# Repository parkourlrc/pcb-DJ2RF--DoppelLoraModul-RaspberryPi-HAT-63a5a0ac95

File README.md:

# English below

# DoppelLoraModul-RaspberryPi-HAT
Raspberry HAT for Nerdverlag LoRa Analyser or any other projects 
# Doppel-LoRa-HAT für Raspberry Pi

Dieses KiCad-Projekt enthält die Schaltung und das Leiterplattenlayout für ein Raspberry-Pi-HAT mit zwei unabhängigen 
LoRa-Funkmodulen auf Basis des **Semtech SX1262**.

Die Platine wurde für den gleichzeitigen Betrieb eines 433-MHz- und eines 863/868-MHz-Moduls entwickelt. 
Beide Funkmodule verwenden den gemeinsamen SPI0-Bus des Raspberry Pi, besitzen jedoch getrennte Chip-Select-, 
Reset-, Busy-, Interrupt- und HF-Umschaltleitungen.

Das HAT ist insbesondere für den Einsatz mit dem **LoRa MeshRadio Analyzer** und weiteren 
Raspberry-Pi-basierten LoRa-Empfangs- und Analyseprojekten vorgesehen.

---

## Unterstützte Funkmodule

Die Platine ist für folgende Waveshare-Core1262-Module ausgelegt:

- **Waveshare Core1262-LF**
  - Frequenzbereich: 410 bis 510 MHz
  - vorgesehen für Anwendungen im 433-MHz-Bereich

- **Waveshare Core1262-HF**
  - Frequenzbereich: 850 bis 930 MHz
  - vorgesehen für Anwendungen im 863-/868-MHz-Bereich

Beide Module basieren auf dem SX1262 und besitzen dieselbe mechanische sowie elektrische Anschlussbelegung.

---

## SPI-Anbindung

Beide SX1262-Module verwenden gemeinsam:

| Signal | Raspberry Pi GPIO | Physischer Pin |
|---|---:|---:|
| SPI0 MOSI | GPIO10 | Pin 19 |
| SPI0 MISO | GPIO9 | Pin 21 |
| SPI0 SCLK | GPIO11 | Pin 23 |

Die Module werden über getrennte Chip-Select-Leitungen angesprochen.

### 863-/868-MHz-Modul

| Funktion | Raspberry Pi GPIO | Physischer Pin |
|---|---:|---:|
| Chip Select | GPIO8 / CE0 | Pin 24 |
| Reset | GPIO22 | Pin 15 |
| Busy | GPIO23 | Pin 16 |
| DIO1 | GPIO24 | Pin 18 |
| RXEN | GPIO25 | Pin 22 |
| TXEN | GPIO5 | Pin 29 |

Linux-Gerät:

/dev/spidev0.0
433-MHz-Modul
Funktion	Raspberry Pi GPIO	Physischer Pin
Chip Select	GPIO7 / CE1	Pin 26
Reset	GPIO17	Pin 11
Busy	GPIO27	Pin 13
DIO1	GPIO18	Pin 12
RXEN	GPIO6	Pin 31
TXEN	GPIO13	Pin 33

Linux-Gerät:

/dev/spidev0.1
Funktionsprinzip

Die beiden LoRa-Module können unabhängig voneinander konfiguriert und gleichzeitig betrieben werden.

Typische Verwendung:

433-MHz-Modul für LoRa-Verbindungen im 70-cm-Bereich
863-/868-MHz-Modul für Sensoren, Telemetrie und ISM-LoRa-Anwendungen
paralleler Empfang auf beiden Frequenzbereichen
Einsatz als Funk-Frontend für den LoRa MeshRadio Analyzer
Entwicklung eigener Raspberry-Pi-LoRa-Anwendungen

Die Antennen werden direkt an den U.FL-/IPEX-Anschlüssen der jeweiligen Core1262-Module angeschlossen.

HAT-ID-EEPROM

Inhalt des Repositorys

Das Repository enthält die wesentlichen KiCad-Projektdateien:

*.kicad_pro
*.kicad_sch
*.kicad_pcb
fp-lib-table
sym-lib-table
Nerdverlag.pretty/

Eigene Symbole und Footprints werden zusammen mit dem Projekt gespeichert, damit der Schaltplan und das
Leiterplattenlayout auch auf anderen Rechnern vollständig geöffnet werden können.

Automatisch erzeugte KiCad-Backups, Sperrdateien und persönliche Arbeitsplatzdateien werden nicht versioniert.

Voraussetzungen

Zum Bearbeiten des Projekts wird eine aktuelle KiCad-Version empfohlen.

Das Projekt wurde mit KiCad 10 erstellt.

Für den späteren Betrieb auf dem Raspberry Pi müssen SPI und die GPIO-Schnittstellen aktiviert sein.

Kontrolle unter Linux:

ls -l /dev/spidev0.0 /dev/spidev0.1
ls -l /dev/gpiochip*

Der verwendete Benutzer sollte Mitglied der Gruppen spi und gpio sein.

Projektstatus

Das Projekt befindet sich in aktiver Entwicklung.

Vor einer Fertigung sollten mindestens folgende Punkte geprüft werden:

KiCad ERC ohne relevante Fehler
KiCad DRC ohne relevante Fehler
korrekte Footprints und Padnummern
ausreichende Leiterbahnbreiten für die Stromversorgung
vollständig gefüllte GND-Flächen
korrekte Bestückungsbezeichnungen für LF- und HF-Modul
mechanische Abstände zum Raspberry Pi
vollständige Gerber- und Bohrdatenausgabe

Eine Fertigung sollte immer auf Grundlage eines abschließend geprüften Versionsstands erfolgen.

Hinweis zum Funkbetrieb

Für den Funkbetrieb gelten die jeweils nationalen Vorschriften zu Frequenzbereichen,
Sendeleistungen, Bandbreiten und zulässigen Anwendungen.

Der Betreiber ist selbst dafür verantwortlich, die gesetzlichen Bestimmungen und
gegebenenfalls die für den Amateurfunk geltenden Regelungen einzuhalten.

Die Platine selbst stellt lediglich die technische Hardwareplattform bereit.

Lizenz und Nutzung

Dieses Projekt ist für eigene Entwicklungs-, Forschungs- und Ausbildungszwecke vorgesehen.

Eine kommerzielle Nutzung, Weitergabe oder Fertigung ist nur nach vorheriger Zustimmung des Rechteinhabers gestattet,
sofern keine separate Lizenzdatei etwas anderes festlegt.

## Author

**Friedrich Riedhammer – DJ2RF**  
**Nerdverlag**

[Visit Nerdverlag](https://nerdverlag.com)

[You can get the Software LoRa Analyser for free](https://nerdverlag.com/?page_id=892)

Email: [fritz@nerdverlag.com](mailto:fritz@nerdverlag.com)

---

© 2026 Nerdverlag  
Friedrich Riedhammer  
All rights reserved.

# English

# Dual LoRa HAT for Raspberry Pi

This KiCad project contains the schematic and PCB layout for a Raspberry Pi HAT with two independent
LoRa radio modules based on the **Semtech SX1262**.

The board was designed for the simultaneous operation of one 433 MHz module and one 863/868 MHz module.
Both radio modules share the Raspberry Pi SPI0 bus, while using separate chip-select,
reset, busy, interrupt, and RF switch control lines.

The HAT is primarily intended for use with the **LoRa MeshRadio Analyzer**
and other Raspberry Pi-based LoRa receiver and analysis projects.

---

## Supported Radio Modules

The board is designed for the following Waveshare Core1262 modules:

- **Waveshare Core1262-LF**
  - Frequency range: 410 to 510 MHz
  - Intended for applications in the 433 MHz range

- **Waveshare Core1262-HF**
  - Frequency range: 850 to 930 MHz
  - Intended for applications in the 863/868 MHz range

Both modules are based on the SX1262 and use the same mechanical and electrical pinout.

---

## SPI Connection

Both SX1262 modules share the following SPI signals:

| Signal | Raspberry Pi GPIO | Physical Pin |
|---|---:|---:|
| SPI0 MOSI | GPIO10 | Pin 19 |
| SPI0 MISO | GPIO9 | Pin 21 |
| SPI0 SCLK | GPIO11 | Pin 23 |

The modules are addressed using separate chip-select lines.

### 863/868 MHz Module

| Function | Raspberry Pi GPIO | Physical Pin |
|---|---:|---:|
| Chip Select | GPIO8 / CE0 | Pin 24 |
| Reset | GPIO22 | Pin 15 |
| Busy | GPIO23 | Pin 16 |
| DIO1 | GPIO24 | Pin 18 |
| RXEN | GPIO25 | Pin 22 |
| TXEN | GPIO5 | Pin 29 |

Linux device:

/dev/spidev0.0
433 MHz Module
Function	Raspberry Pi GPIO	Physical Pin
Chip Select	GPIO7 / CE1	Pin 26
Reset	GPIO17	Pin 11
Busy	GPIO27	Pin 13
DIO1	GPIO18	Pin 12
RXEN	GPIO6	Pin 31
TXEN	GPIO13	Pin 33

Linux device:

/dev/spidev0.1
Operating Principle

The two LoRa modules can be configured independently and operated at the same time.

Typical applications include:

433 MHz LoRa communication in the 70 cm band
863/868 MHz sensor, telemetry, and ISM LoRa applications
Simultaneous reception in both frequency ranges
Use as a radio frontend for the LoRa MeshRadio Analyzer
Development of custom Raspberry Pi LoRa applications

The antennas are connected directly to the U.FL/IPEX connectors on the respective Core1262 modules.

Repository Contents

The repository contains the essential KiCad project files:

*.kicad_pro
*.kicad_sch
*.kicad_pcb
fp-lib-table
sym-lib-table
Nerdverlag.pretty/

Custom symbols and footprints are stored together with the project so that the schematic and PCB layout
can also be opened completely on another computer.

Automatically generated KiCad backups, lock files, and personal workspace files are not included in version control.

Requirements

A current version of KiCad is recommended for editing the project.

The project was created with KiCad 10.

For operation on a Raspberry Pi, SPI and the GPIO interfaces must be enabled.

Check the available devices under Linux:

ls -l /dev/spidev0.0 /dev/spidev0.1
ls -l /dev/gpiochip*

The user running the software should be a member of the spi and gpio groups.

Project Status

This project is under active development.

Before manufacturing the board, at least the following points should be checked:

KiCad ERC completed without relevant errors
KiCad DRC completed without relevant errors
Correct footprints and pad numbering
Sufficient track widths for the power supply
Completely filled GND planes
Correct component designations for the LF and HF modules
Mechanical clearance to the Raspberry Pi
Complete Gerber and drill file output

Manufacturing should always be based on a final, fully verified version of the project.

Radio Operation Notice

Radio operation is subject to the applicable national regulations concerning frequency ranges, transmission power,
bandwidth, duty cycle, and permitted applications.

The operator is responsible for complying with all applicable legal requirements and, where relevant, amateur radio regulations.

The board itself only provides the technical hardware platform.

License and Use

This project is intended for personal development, research, and educational purposes.

Commercial use, redistribution, or manufacturing requires prior permission from the copyright holder unless
a separate license file explicitly permits such use.

## Author

**Friedrich Riedhammer – DJ2RF**  
**Nerdverlag**

[Visit Nerdverlag](https://nerdverlag.com)

[You can get the Software LoRa Analyser for free](https://nerdverlag.com/?page_id=901&lang=en)

Email: [fritz@nerdverlag.com](mailto:fritz@nerdverlag.com)

---

© 2026 Nerdverlag  
Friedrich Riedhammer  
All rights reserved.

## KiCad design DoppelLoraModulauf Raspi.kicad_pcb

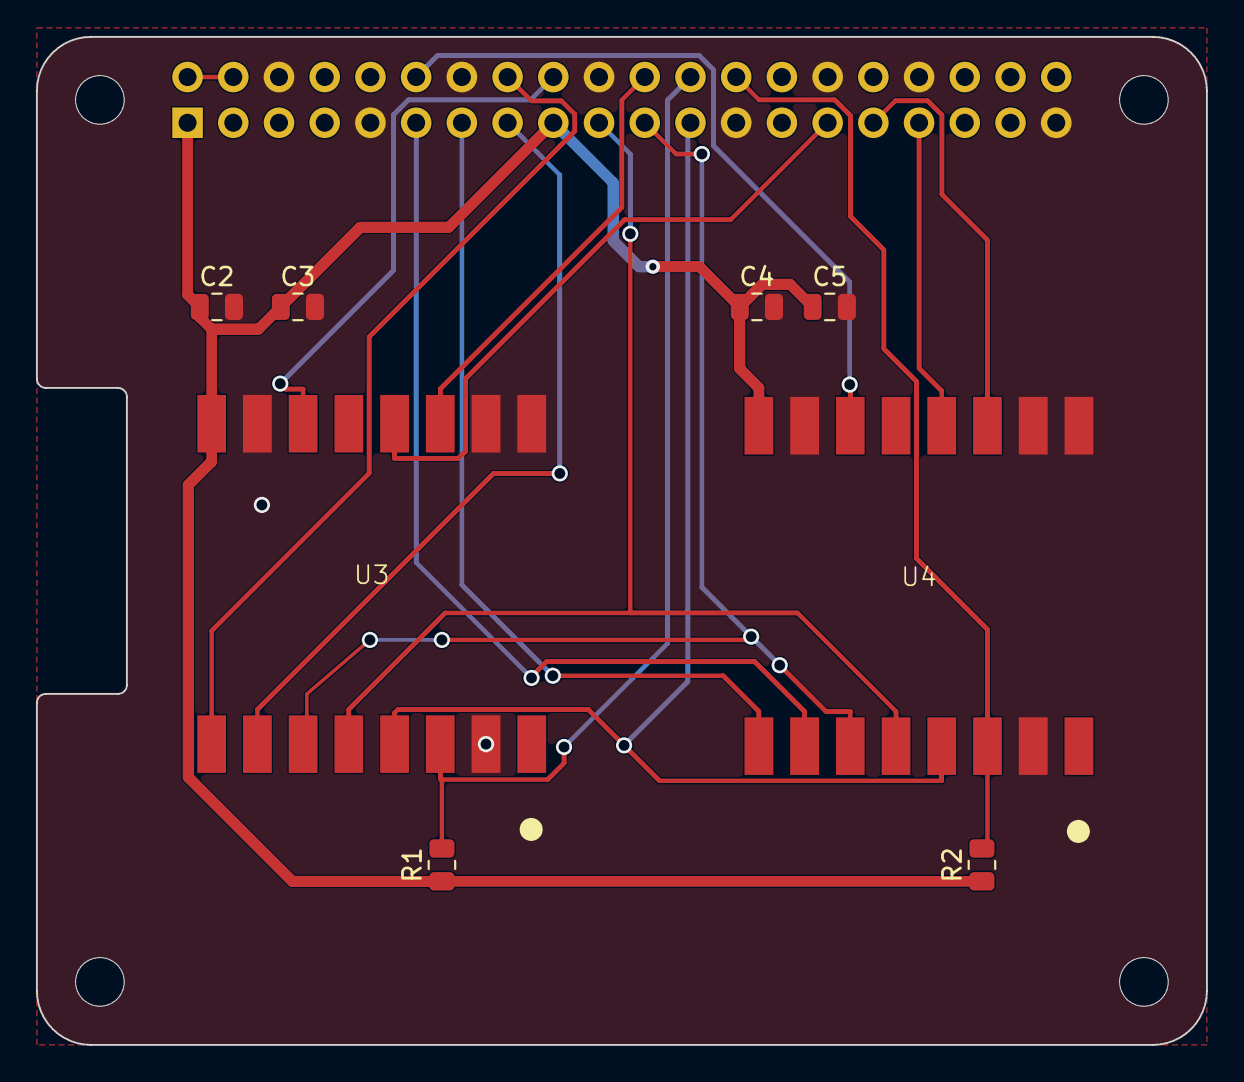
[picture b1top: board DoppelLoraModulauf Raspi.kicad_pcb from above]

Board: 2 copper layers, 65.0 x 56.0 mm, 13 parts (1 on the bottom side), 17 nets.

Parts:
C2, C3, C4, C5: C; C_0805_2012Metric
J1: Conn_02x20_Odd_Even; PinSocket_2x20_P2.54mm_Vertical
MH1, MH2, MH3, MH4: MountingHole_2.7mm_M2.5
R1, R2: 10k; R_0805_2012Metric
U3, U4: Waveshare_Core1262_HF_LF

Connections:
+3V3: C2.1, C3.1, C4.1, C5.1, J1.1, J1.17, R1.1, R2.1, U3.9 (+3V3), U4.9 (+3V3)
/GPIO5: J1.29, U3.13 (TXEN)
/GPIO6: J1.31, U4.14 (RXEN)
/GPIO7/SPI0.CE1: J1.26, R2.2, U4.3 (CS)
/GPIO8/SPI0.CE0: J1.24, R1.2, U3.3 (CS)
/GPIO9/SPI0.MISO: J1.21, U3.6 (MISO), U4.6 (MISO)
/GPIO10/SPI0.MOSI: J1.19, U3.5 (MOSI), U4.5 (MOSI)
/GPIO11/SPI0.SCLK: J1.23, U3.4 (CLK), U4.4 (CLK)
/GPIO13/PWM1: J1.33, U4.13 (TXEN)
/GPIO17: J1.11, U4.7 (RESET)
/GPIO18/PCM.CLK: J1.12, U4.11 (DIO1)
/GPIO22: J1.15, U3.7 (RESET)
/GPIO23: J1.16, U3.8 (BUSY)
/GPIO24: J1.18, U3.11 (DIO1)
/GPIO25: J1.22, U3.14 (RXEN)
/GPIO27: J1.13, U4.8 (BUSY)
GND: C2.2, C3.2, C4.2, C5.2, J1.6, J1.9, J1.14, J1.20, J1.25, J1.30, J1.34, J1.39, U3.2 (GND), U3.10 (GND), U3.15 (GND), U3.16 (GND), U4.2 (GND), U4.10 (GND), U4.15 (GND), U4.16 (GND)
